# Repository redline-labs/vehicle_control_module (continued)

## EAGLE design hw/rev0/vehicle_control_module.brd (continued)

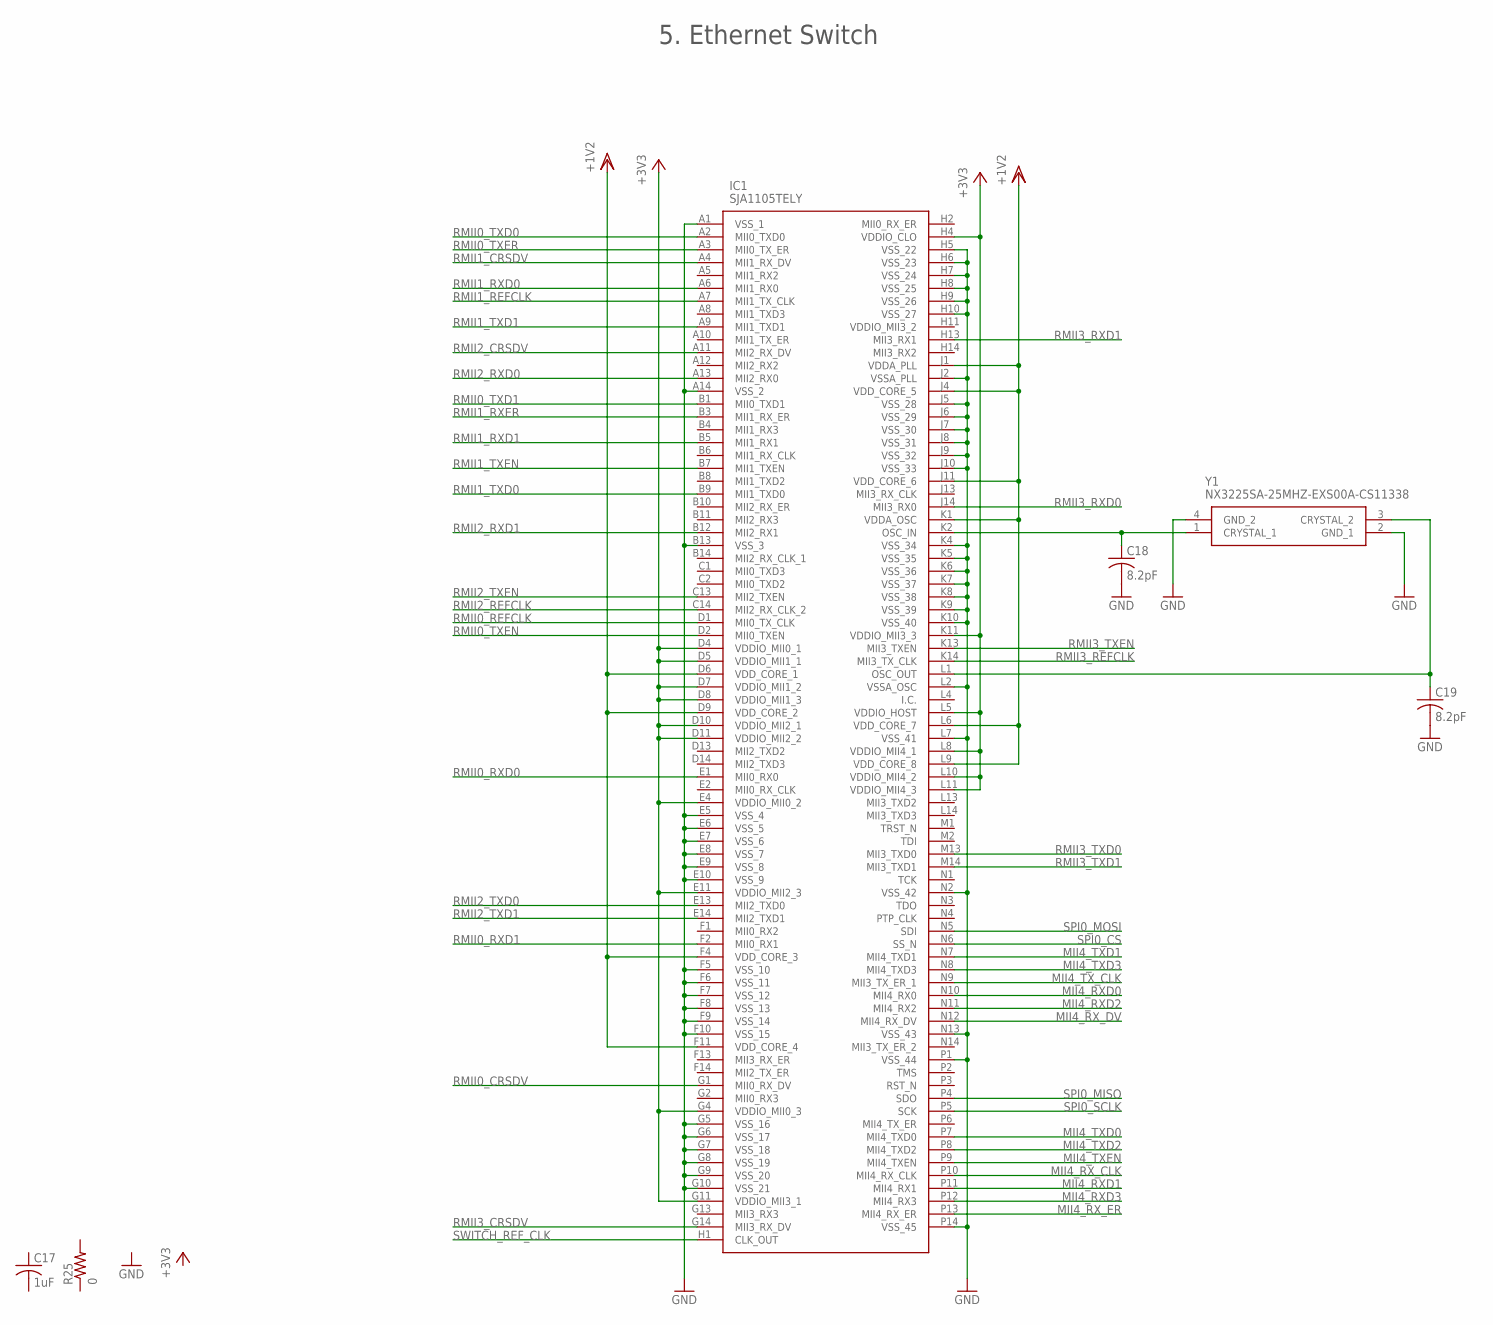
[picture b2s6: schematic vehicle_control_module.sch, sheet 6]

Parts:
C17: 1uF; C0603
C18, C19: 8.2pF; C0603
IC1: SJA1105TELY; BGA159C80P14X14_1200X1200X150
R25: 0; R0603
Y1: NX3225SA-25MHZ-EXS00A-CS11338; NX3225SA25MHZEXS00ACS11338

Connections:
+3V3: IC1.D4 (VDDIO_MII0_1), IC1.D5 (VDDIO_MII1_1), IC1.D7 (VDDIO_MII1_2), IC1.D8 (VDDIO_MII1_3), IC1.D10 (VDDIO_MII2_1), IC1.D11 (VDDIO_MII2_2), IC1.E4 (VDDIO_MII0_2), IC1.E11 (VDDIO_MII2_3), IC1.G4 (VDDIO_MII0_3), IC1.G11 (VDDIO_MII3_1), IC1.H4 (VDDIO_CLO), IC1.K11 (VDDIO_MII3_3), IC1.L5 (VDDIO_HOST), IC1.L8 (VDDIO_MII4_1), IC1.L10 (VDDIO_MII4_2), IC1.L11 (VDDIO_MII4_3); also elsewhere on the board
GND: C18.2, C19.2, IC1.A1 (VSS_1), IC1.A14 (VSS_2), IC1.B13 (VSS_3), IC1.E5 (VSS_4), IC1.E6 (VSS_5), IC1.E7 (VSS_6), IC1.E8 (VSS_7), IC1.E9 (VSS_8), IC1.E10 (VSS_9), IC1.F5 (VSS_10), IC1.F6 (VSS_11), IC1.F7 (VSS_12), IC1.F8 (VSS_13), IC1.F9 (VSS_14), IC1.F10 (VSS_15), IC1.G5 (VSS_16), IC1.G6 (VSS_17), IC1.G7 (VSS_18), IC1.G8 (VSS_19), IC1.G9 (VSS_20), IC1.G10 (VSS_21), IC1.H5 (VSS_22), IC1.H6 (VSS_23), IC1.H7 (VSS_24), IC1.H8 (VSS_25), IC1.H9 (VSS_26), IC1.H10 (VSS_27), IC1.J2 (VSSA_PLL), IC1.J5 (VSS_28), IC1.J6 (VSS_29), IC1.J7 (VSS_30), IC1.J8 (VSS_31), IC1.J9 (VSS_32), IC1.J10 (VSS_33), IC1.K4 (VSS_34), IC1.K5 (VSS_35), IC1.K6 (VSS_36), IC1.K7 (VSS_37), IC1.K8 (VSS_38), IC1.K9 (VSS_39), IC1.K10 (VSS_40), IC1.L2 (VSSA_OSC), IC1.L7 (VSS_41), IC1.N2 (VSS_42), IC1.N13 (VSS_43), IC1.P1 (VSS_44), IC1.P14 (VSS_45), Y1.2 (GND_1), Y1.4 (GND_2); also elsewhere on the board
MII4_RXD0: IC1.N10 (MII4_RX0); also elsewhere on the board
MII4_RXD1: IC1.P11 (MII4_RX1); also elsewhere on the board
MII4_RXD2: IC1.N11 (MII4_RX2); also elsewhere on the board
MII4_RXD3: IC1.P12 (MII4_RX3); also elsewhere on the board
MII4_RX_CLK: IC1.P10 (MII4_RX_CLK); also elsewhere on the board
MII4_RX_DV: IC1.N12 (MII4_RX_DV); also elsewhere on the board
MII4_RX_ER: IC1.P13 (MII4_RX_ER)
MII4_TXD0: IC1.P7 (MII4_TXD0); also elsewhere on the board
MII4_TXD1: IC1.N7 (MII4_TXD1); also elsewhere on the board
MII4_TXD2: IC1.P8 (MII4_TXD2); also elsewhere on the board
MII4_TXD3: IC1.N8 (MII4_TXD3); also elsewhere on the board
MII4_TXEN: IC1.P9 (MII4_TXEN); also elsewhere on the board
MII4_TX_CLK: IC1.N9 (MII3_TX_ER_1); also elsewhere on the board
unnamed: C18.1, IC1.K2 (OSC_IN), Y1.1 (CRYSTAL_1)
unnamed: C19.1, IC1.L1 (OSC_OUT), Y1.3 (CRYSTAL_2)
RMII0_CRSDV: IC1.G1 (MII0_RX_DV); also elsewhere on the board
RMII0_REFCLK: IC1.D1 (MII0_TX_CLK); also elsewhere on the board
RMII0_RXD0: IC1.E1 (MII0_RX0); also elsewhere on the board
RMII0_RXD1: IC1.F2 (MII0_RX1); also elsewhere on the board
RMII0_TXD0: IC1.A2 (MII0_TXD0); also elsewhere on the board
RMII0_TXD1: IC1.B1 (MII0_TXD1); also elsewhere on the board
RMII0_TXEN: IC1.D2 (MII0_TXEN); also elsewhere on the board
RMII0_TXER: IC1.A3 (MII0_TX_ER); also elsewhere on the board
RMII1_CRSDV: IC1.A4 (MII1_RX_DV); also elsewhere on the board
RMII1_REFCLK: IC1.A7 (MII1_TX_CLK); also elsewhere on the board
RMII1_RXD0: IC1.A6 (MII1_RX0); also elsewhere on the board
RMII1_RXD1: IC1.B5 (MII1_RX1); also elsewhere on the board
RMII1_RXER: IC1.B3 (MII1_RX_ER); also elsewhere on the board
RMII1_TXD0: IC1.B9 (MII1_TXD0); also elsewhere on the board
RMII1_TXD1: IC1.A9 (MII1_TXD1); also elsewhere on the board
RMII1_TXEN: IC1.B7 (MII1_TXEN)
RMII2_CRSDV: IC1.A11 (MII2_RX_DV); also elsewhere on the board
RMII2_REFCLK: IC1.C14 (MII2_RX_CLK_2); also elsewhere on the board
RMII2_RXD0: IC1.A13 (MII2_RX0); also elsewhere on the board
RMII2_RXD1: IC1.B12 (MII2_RX1); also elsewhere on the board
RMII2_TXD0: IC1.E13 (MII2_TXD0); also elsewhere on the board
RMII2_TXD1: IC1.E14 (MII2_TXD1); also elsewhere on the board
RMII2_TXEN: IC1.C13 (MII2_TXEN)
RMII3_CRSDV: IC1.G14 (MII3_RX_DV); also elsewhere on the board
RMII3_REFCLK: IC1.K14 (MII3_TX_CLK); also elsewhere on the board
RMII3_RXD0: IC1.J14 (MII3_RX0); also elsewhere on the board
RMII3_RXD1: IC1.H13 (MII3_RX1); also elsewhere on the board
RMII3_TXD0: IC1.M13 (MII3_TXD0); also elsewhere on the board
RMII3_TXD1: IC1.M14 (MII3_TXD1); also elsewhere on the board
RMII3_TXEN: IC1.K13 (MII3_TXEN)
SPI0_CS: IC1.N6 (SS_N); also elsewhere on the board
SPI0_MISO: IC1.P4 (SDO); also elsewhere on the board
SPI0_MOSI: IC1.N5 (SDI); also elsewhere on the board
SPI0_SCLK: IC1.P5 (SCK); also elsewhere on the board
SWITCH_REF_CLK: IC1.H1 (CLK_OUT); also elsewhere on the board
VDD: IC1.D6 (VDD_CORE_1), IC1.D9 (VDD_CORE_2), IC1.F4 (VDD_CORE_3), IC1.F11 (VDD_CORE_4), IC1.J1 (VDDA_PLL), IC1.J4 (VDD_CORE_5), IC1.J11 (VDD_CORE_6), IC1.K1 (VDDA_OSC), IC1.L6 (VDD_CORE_7), IC1.L9 (VDD_CORE_8); also elsewhere on the board

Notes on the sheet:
5. Ethernet Switch

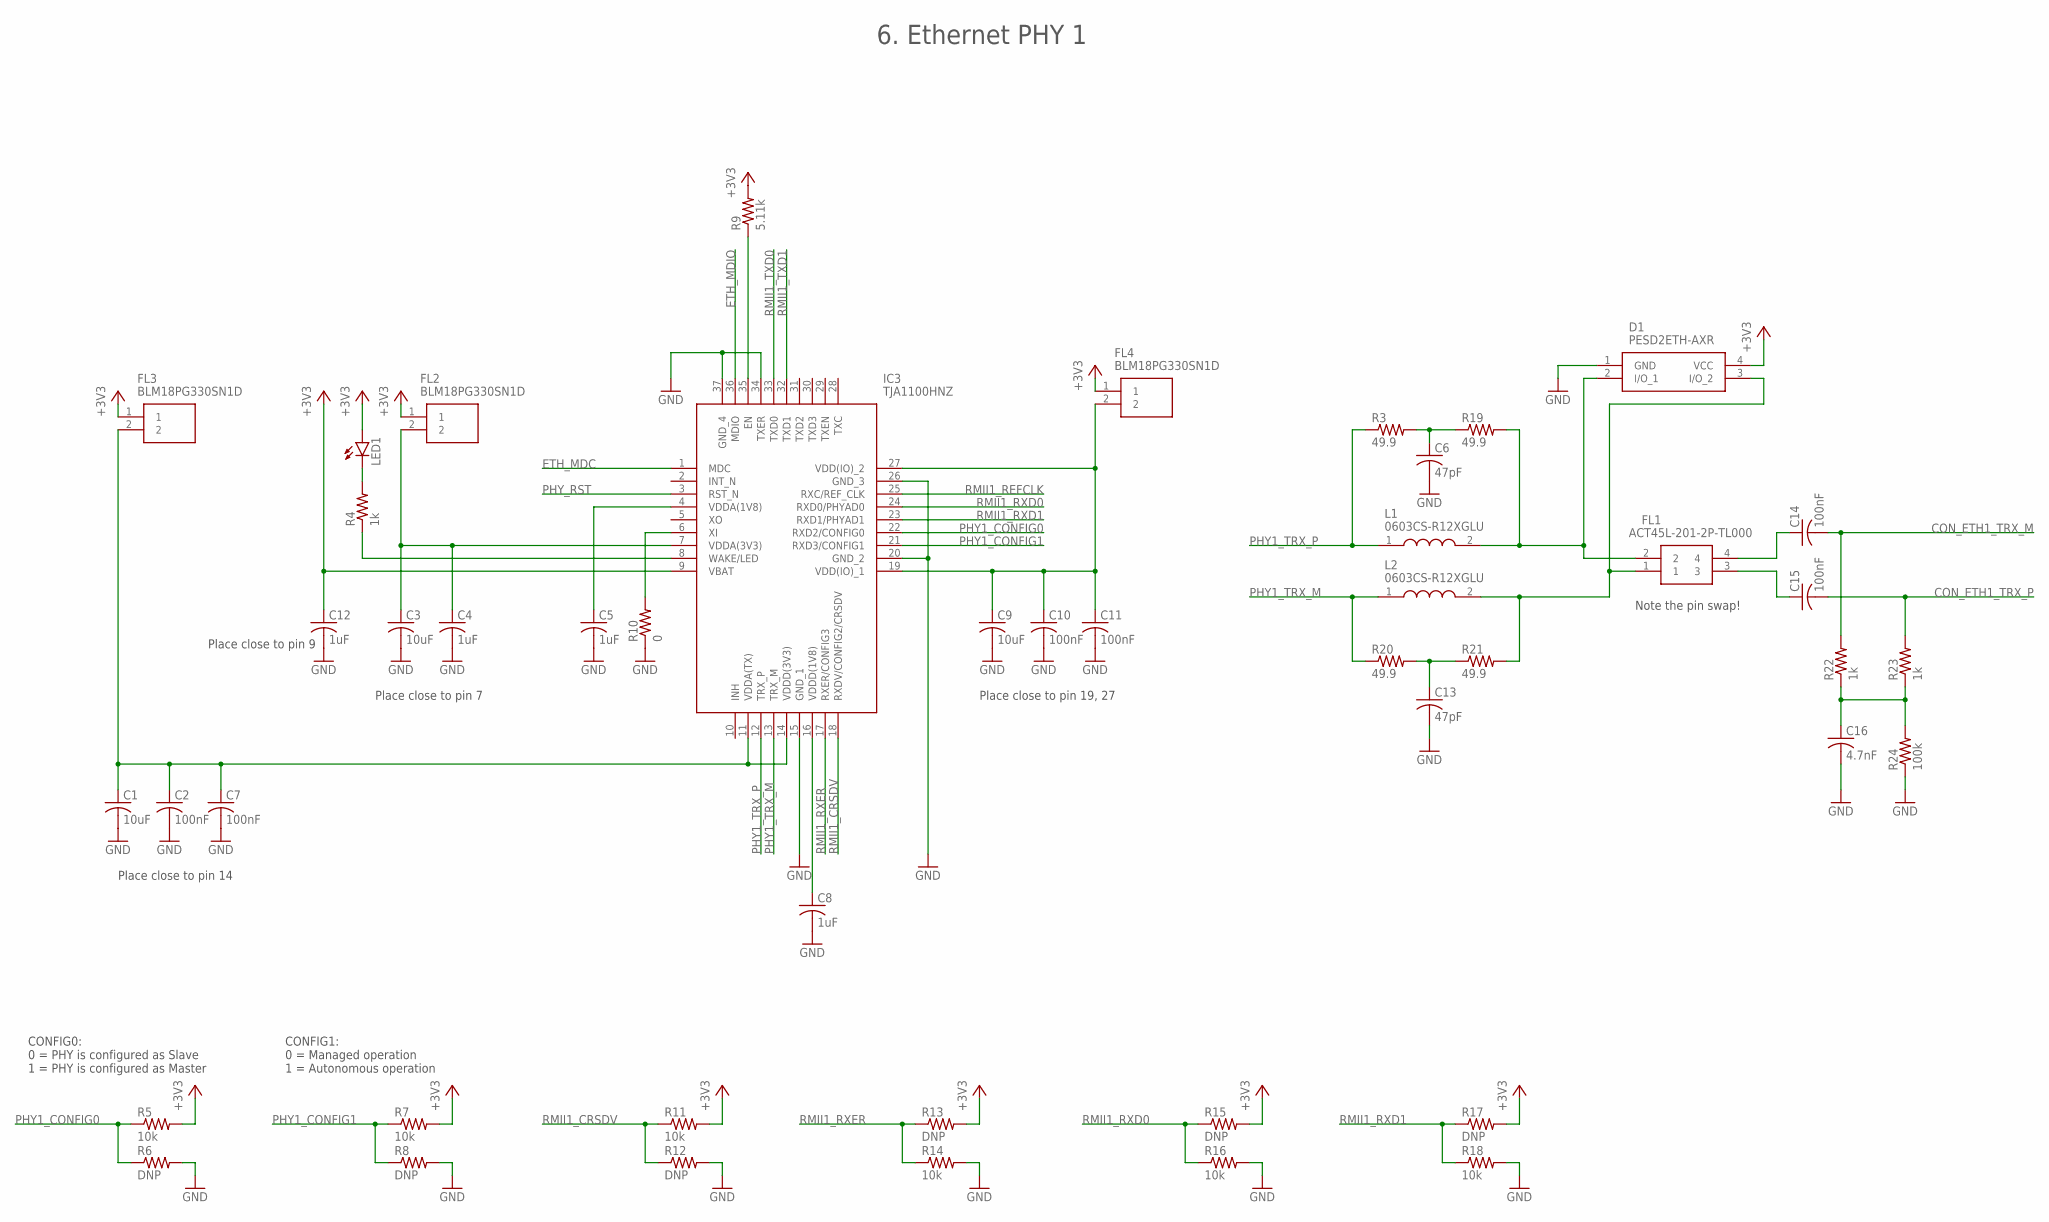
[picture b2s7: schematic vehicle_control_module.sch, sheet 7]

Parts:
C1, C3, C9: 10uF; C0603
C2, C7, C10, C11, C14, C15: 100nF; C0603
C4, C5, C8, C12: 1uF; C0603
C6, C13: 47pF; C0603
C16: 4.7nF; C0603
D1: PESD2ETH-AXR; PESD2ETHAXR
FL1: ACT45L-201-2P-TL000; ACT45L_1
FL2, FL3, FL4: BLM18PG330SN1D; BEADC1608X95N
IC3: TJA1100HNZ; QFN50P600X600X100-37N
L1, L2: 0603CS-R12XGLU; 0603CS82NXGLW
LED1: LEDCHIPLED_0603; CHIPLED_0603
R3, R19, R20, R21: 49.9; R0603
R4, R22, R23: 1k; R0603
R5, R7, R11, R14, R16, R18: 10k; R0603
R6, R8, R12, R13, R15, R17: DNP; R0603
R9: 5.11k; R0603
R10: 0; R0603
R24: 100k; R0603

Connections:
+3V3: C12.1, D1.4 (VCC), FL2.1, FL3.1, FL4.1, IC3.9 (VBAT), LED1.A, R5.2, R7.2, R9.2, R11.2, R13.2, R15.2, R17.2; also elsewhere on the board
CON_ETH1_TRX_M: C14.2, R22.2
CON_ETH1_TRX_P: C15.2, R23.2
ETH_MDC: IC3.1 (MDC); also elsewhere on the board
ETH_MDIO: IC3.36 (MDIO); also elsewhere on the board
GND: C1.2, C2.2, C3.2, C4.2, C5.2, C6.2, C7.2, C8.2, C9.2, C10.2, C11.2, C12.2, C13.2, C16.2, D1.1 (GND), IC3.15 (GND_1), IC3.20 (GND_2), IC3.26 (GND_3), IC3.34 (TXER), IC3.37 (GND_4), R6.2, R8.2, R10.1, R12.2, R14.2, R16.2, R18.2, R24.1; also elsewhere on the board
unnamed: LED1.C, R4.2
unnamed: C5.1, IC3.4 (VDDA(1V8))
unnamed: IC3.8 (WAKE/LED), R4.1
unnamed: C8.1, IC3.16 (VDDD(1V8))
unnamed: C3.1, C4.1, FL2.2, IC3.7 (VDDA(3V3))
unnamed: C1.1, C2.1, C7.1, FL3.2, IC3.11 (VDDA(TX)), IC3.14 (VDDD(3V3))
unnamed: C9.1, C10.1, C11.1, FL4.2, IC3.19 (VDD(IO)_1), IC3.27 (VDD(IO)_2)
unnamed: IC3.35 (EN), R9.1
unnamed: IC3.6 (XI), R10.2
unnamed: D1.3 (I/O_2), FL1.1, L2.2, R21.2
unnamed: D1.2 (I/O_1), FL1.2, L1.2, R19.2
unnamed: C6.1, R3.2, R19.1
unnamed: C13.1, R20.2, R21.1
unnamed: C14.1, FL1.4
unnamed: C15.1, FL1.3
unnamed: C16.1, R22.1, R23.1, R24.2
PHY1_CONFIG0: IC3.22 (RXD2/CONFIG0), R5.1, R6.1
PHY1_CONFIG1: IC3.21 (RXD3/CONFIG1), R7.1, R8.1
PHY1_TRX_M: IC3.13 (TRX_M), L2.1, R20.1
PHY1_TRX_P: IC3.12 (TRX_P), L1.1, R3.1
PHY_RST: IC3.3 (RST_N); also elsewhere on the board
RMII1_CRSDV: IC3.18 (RXDV/CONFIG2/CRSDV), R11.1, R12.1; also elsewhere on the board
RMII1_REFCLK: IC3.25 (RXC/REF_CLK); also elsewhere on the board
RMII1_RXD0: IC3.24 (RXD0/PHYAD0), R15.1, R16.1; also elsewhere on the board
RMII1_RXD1: IC3.23 (RXD1/PHYAD1), R17.1, R18.1; also elsewhere on the board
RMII1_RXER: IC3.17 (RXER/CONFIG3), R13.1, R14.1; also elsewhere on the board
RMII1_TXD0: IC3.33 (TXD0); also elsewhere on the board
RMII1_TXD1: IC3.32 (TXD1); also elsewhere on the board

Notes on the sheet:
Place close to pin 7
Place close to pin 9
Place close to pin 14
Place close to pin 19, 27
CONFIG0: 0 = PHY is configured as Slave 1 = PHY is configured as Master
CONFIG1: 0 = Managed operation 1 = Autonomous operation
Note the pin swap!
6. Ethernet PHY 1

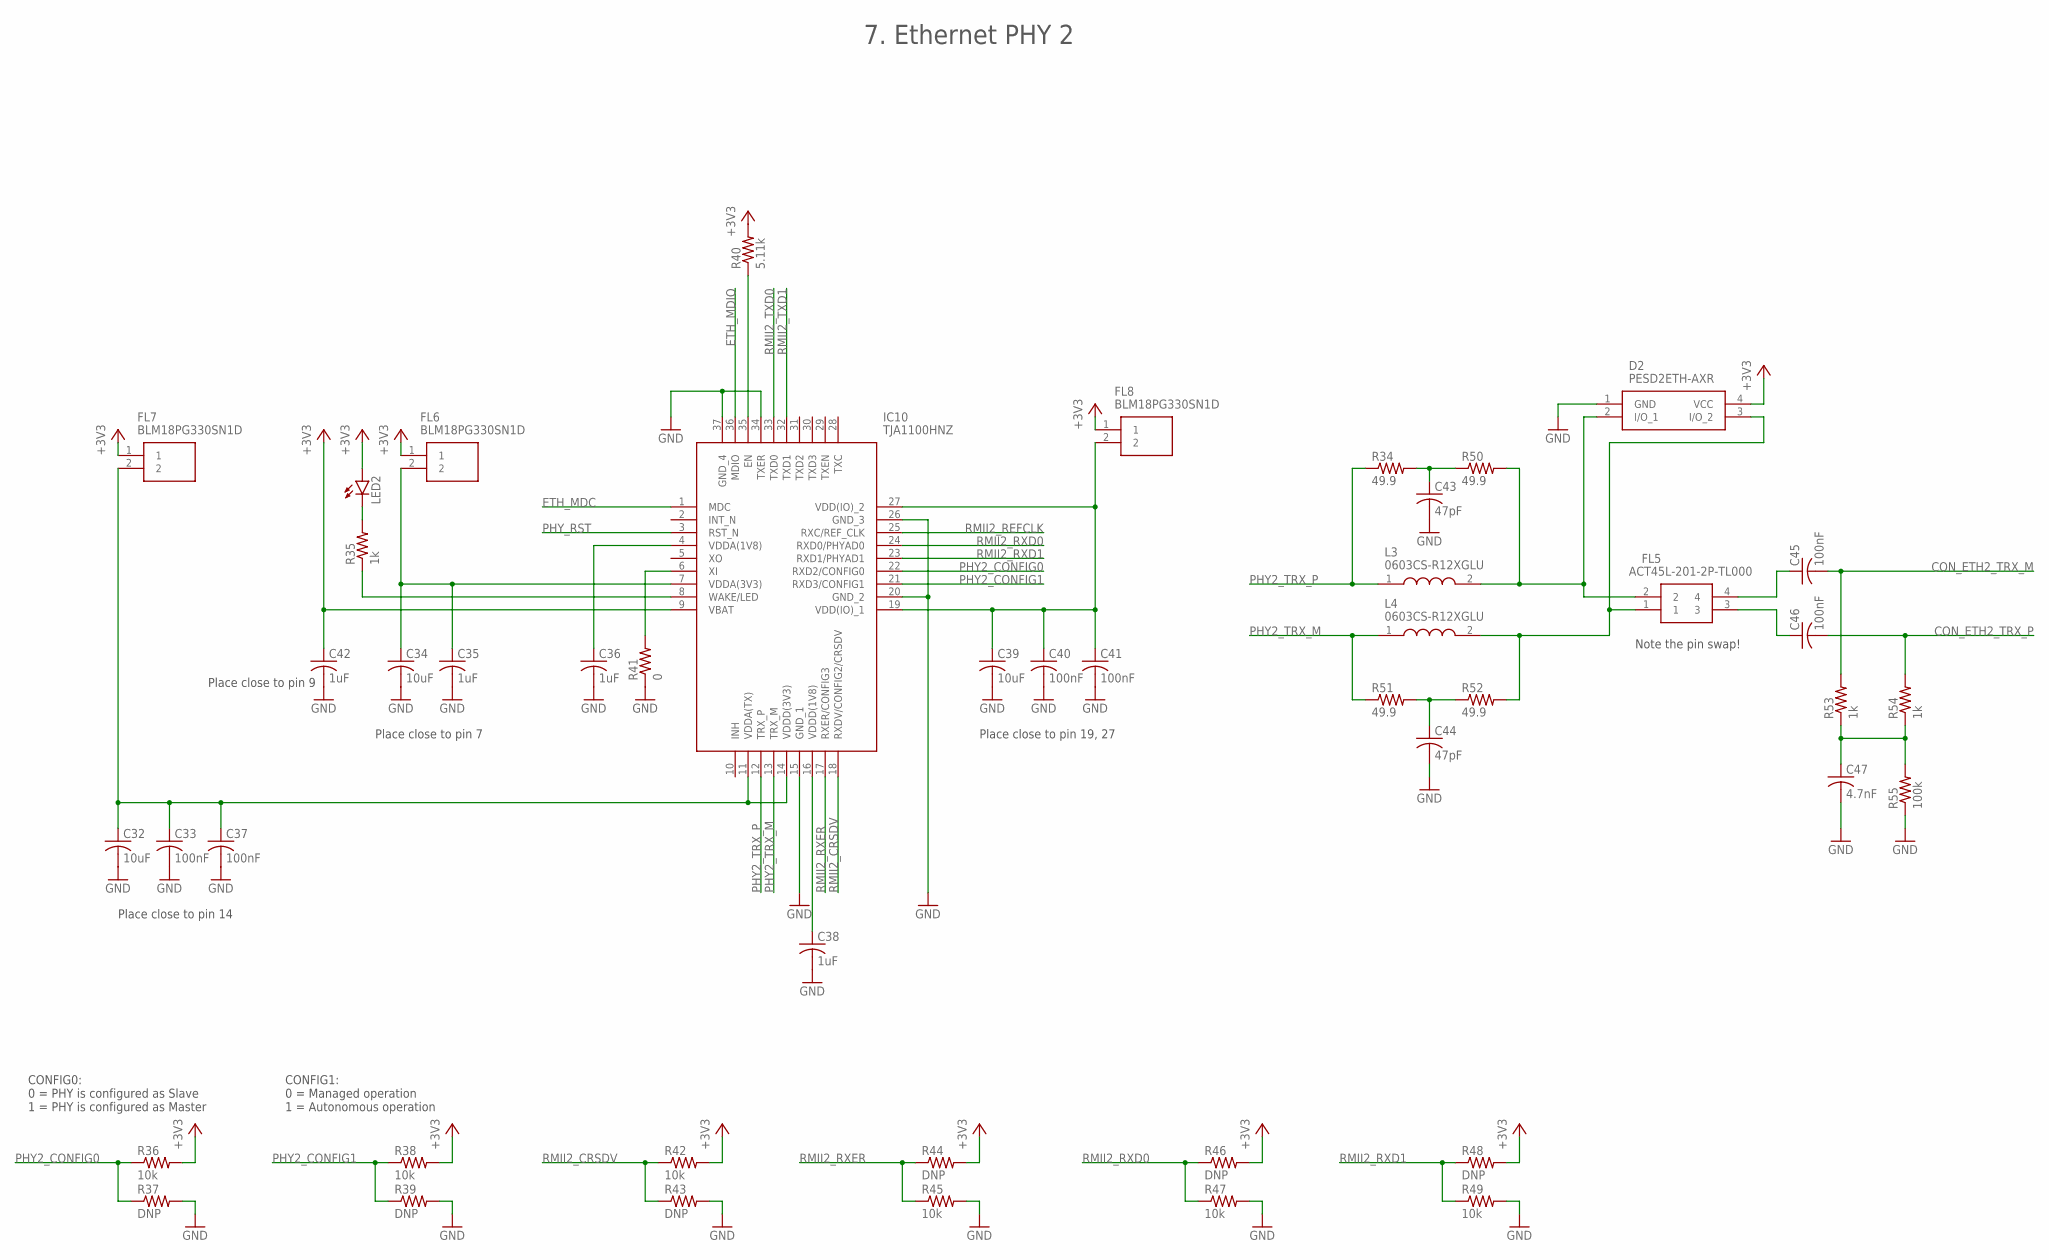
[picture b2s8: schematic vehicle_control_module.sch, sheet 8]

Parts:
C32, C34, C39: 10uF; C0603
C33, C37, C40, C41, C45, C46: 100nF; C0603
C35, C36, C38, C42: 1uF; C0603
C43, C44: 47pF; C0603
C47: 4.7nF; C0603
D2: PESD2ETH-AXR; PESD2ETHAXR
FL5: ACT45L-201-2P-TL000; ACT45L_1
FL6, FL7, FL8: BLM18PG330SN1D; BEADC1608X95N
IC10: TJA1100HNZ; QFN50P600X600X100-37N
L3, L4: 0603CS-R12XGLU; 0603CS82NXGLW
LED2: LEDCHIPLED_0603; CHIPLED_0603
R34, R50, R51, R52: 49.9; R0603
R35, R53, R54: 1k; R0603
R36, R38, R42, R45, R47, R49: 10k; R0603
R37, R39, R43, R44, R46, R48: DNP; R0603
R40: 5.11k; R0603
R41: 0; R0603
R55: 100k; R0603

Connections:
+3V3: C42.1, D2.4 (VCC), FL6.1, FL7.1, FL8.1, IC10.9 (VBAT), LED2.A, R36.2, R38.2, R40.2, R42.2, R44.2, R46.2, R48.2; also elsewhere on the board
CON_ETH2_TRX_M: C45.2, R53.2
CON_ETH2_TRX_P: C46.2, R54.2
ETH_MDC: IC10.1 (MDC); also elsewhere on the board
ETH_MDIO: IC10.36 (MDIO); also elsewhere on the board
GND: C32.2, C33.2, C34.2, C35.2, C36.2, C37.2, C38.2, C39.2, C40.2, C41.2, C42.2, C43.2, C44.2, C47.2, D2.1 (GND), IC10.15 (GND_1), IC10.20 (GND_2), IC10.26 (GND_3), IC10.34 (TXER), IC10.37 (GND_4), R37.2, R39.2, R41.1, R43.2, R45.2, R47.2, R49.2, R55.1; also elsewhere on the board
unnamed: LED2.C, R35.2
unnamed: IC10.8 (WAKE/LED), R35.1
unnamed: C36.1, IC10.4 (VDDA(1V8))
unnamed: C38.1, IC10.16 (VDDD(1V8))
unnamed: C34.1, C35.1, FL6.2, IC10.7 (VDDA(3V3))
unnamed: C32.1, C33.1, C37.1, FL7.2, IC10.11 (VDDA(TX)), IC10.14 (VDDD(3V3))
unnamed: C39.1, C40.1, C41.1, FL8.2, IC10.19 (VDD(IO)_1), IC10.27 (VDD(IO)_2)
unnamed: IC10.35 (EN), R40.1
unnamed: IC10.6 (XI), R41.2
unnamed: D2.3 (I/O_2), FL5.1, L4.2, R52.2
unnamed: D2.2 (I/O_1), FL5.2, L3.2, R50.2
unnamed: C43.1, R34.2, R50.1
unnamed: C44.1, R51.2, R52.1
unnamed: C45.1, FL5.4
unnamed: C46.1, FL5.3
unnamed: C47.1, R53.1, R54.1, R55.2
PHY2_CONFIG0: IC10.22 (RXD2/CONFIG0), R36.1, R37.1
PHY2_CONFIG1: IC10.21 (RXD3/CONFIG1), R38.1, R39.1
PHY2_TRX_M: IC10.13 (TRX_M), L4.1, R51.1
PHY2_TRX_P: IC10.12 (TRX_P), L3.1, R34.1
PHY_RST: IC10.3 (RST_N); also elsewhere on the board
RMII2_CRSDV: IC10.18 (RXDV/CONFIG2/CRSDV), R42.1, R43.1; also elsewhere on the board
RMII2_REFCLK: IC10.25 (RXC/REF_CLK); also elsewhere on the board
RMII2_RXD0: IC10.24 (RXD0/PHYAD0), R46.1, R47.1; also elsewhere on the board
RMII2_RXD1: IC10.23 (RXD1/PHYAD1), R48.1, R49.1; also elsewhere on the board
RMII2_RXER: IC10.17 (RXER/CONFIG3), R44.1, R45.1
RMII2_TXD0: IC10.33 (TXD0); also elsewhere on the board
RMII2_TXD1: IC10.32 (TXD1); also elsewhere on the board

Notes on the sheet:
Place close to pin 7
Place close to pin 9
Place close to pin 14
Place close to pin 19, 27
CONFIG0: 0 = PHY is configured as Slave 1 = PHY is configured as Master
CONFIG1: 0 = Managed operation 1 = Autonomous operation
Note the pin swap!
7. Ethernet PHY 2

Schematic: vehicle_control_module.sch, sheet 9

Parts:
C48, C50, C55: 10uF; C0603
C49, C53, C56, C57, C61, C62: 100nF; C0603
C51, C52, C54, C58: 1uF; C0603
C59, C60: 47pF; C0603
C63: 4.7nF; C0603
D3: PESD2ETH-AXR; PESD2ETHAXR
FL9: ACT45L-201-2P-TL000; ACT45L_1
FL10, FL11, FL12: BLM18PG330SN1D; BEADC1608X95N
IC12: TJA1100HNZ; QFN50P600X600X100-37N
L5, L6: 0603CS-R12XGLU; 0603CS82NXGLW
LED3: LEDCHIPLED_0603; CHIPLED_0603
R56, R72, R73, R74: 49.9; R0603
R57, R75, R76: 1k; R0603
R58, R60, R64, R67, R69, R71: 10k; R0603
R59, R61, R65, R66, R68, R70: DNP; R0603
R62: 5.11k; R0603
R63: 0; R0603
R77: 100k; R0603

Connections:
+3V3: C58.1, D3.4 (VCC), FL10.1, FL11.1, FL12.1, IC12.9 (VBAT), LED3.A, R58.2, R60.2, R62.2, R64.2, R66.2, R68.2, R70.2; also elsewhere on the board
CON_ETH3_TRX_M: C61.2, R75.2
CON_ETH3_TRX_P: C62.2, R76.2
ETH_MDC: IC12.1 (MDC); also elsewhere on the board
ETH_MDIO: IC12.36 (MDIO); also elsewhere on the board
GND: C48.2, C49.2, C50.2, C51.2, C52.2, C53.2, C54.2, C55.2, C56.2, C57.2, C58.2, C59.2, C60.2, C63.2, D3.1 (GND), IC12.15 (GND_1), IC12.20 (GND_2), IC12.26 (GND_3), IC12.34 (TXER), IC12.37 (GND_4), R59.2, R61.2, R63.1, R65.2, R67.2, R69.2, R71.2, R77.1; also elsewhere on the board
unnamed: LED3.C, R57.2
unnamed: IC12.8 (WAKE/LED), R57.1
unnamed: C52.1, IC12.4 (VDDA(1V8))
unnamed: C54.1, IC12.16 (VDDD(1V8))
unnamed: C50.1, C51.1, FL10.2, IC12.7 (VDDA(3V3))
unnamed: C48.1, C49.1, C53.1, FL11.2, IC12.11 (VDDA(TX)), IC12.14 (VDDD(3V3))
unnamed: C55.1, C56.1, C57.1, FL12.2, IC12.19 (VDD(IO)_1), IC12.27 (VDD(IO)_2)
unnamed: IC12.35 (EN), R62.1
unnamed: IC12.6 (XI), R63.2
unnamed: D3.3 (I/O_2), FL9.1, L6.2, R74.2
unnamed: D3.2 (I/O_1), FL9.2, L5.2, R72.2
unnamed: C59.1, R56.2, R72.1
unnamed: C60.1, R73.2, R74.1
unnamed: C61.1, FL9.4
unnamed: C62.1, FL9.3
unnamed: C63.1, R75.1, R76.1, R77.2
PHY3_CONFIG0: IC12.22 (RXD2/CONFIG0), R58.1, R59.1
PHY3_CONFIG1: IC12.21 (RXD3/CONFIG1), R60.1, R61.1
PHY3_TRX_M: IC12.13 (TRX_M), L6.1, R73.1
PHY3_TRX_P: IC12.12 (TRX_P), L5.1, R56.1
PHY_RST: IC12.3 (RST_N); also elsewhere on the board
RMII3_CRSDV: IC12.18 (RXDV/CONFIG2/CRSDV), R64.1, R65.1; also elsewhere on the board
RMII3_REFCLK: IC12.25 (RXC/REF_CLK); also elsewhere on the board
RMII3_RXD0: IC12.24 (RXD0/PHYAD0), R68.1, R69.1; also elsewhere on the board
RMII3_RXD1: IC12.23 (RXD1/PHYAD1), R70.1, R71.1; also elsewhere on the board
RMII3_RXER: IC12.17 (RXER/CONFIG3), R66.1, R67.1
RMII3_TXD0: IC12.33 (TXD0); also elsewhere on the board
RMII3_TXD1: IC12.32 (TXD1); also elsewhere on the board

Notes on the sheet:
Place close to pin 7
Place close to pin 9
Place close to pin 14
Place close to pin 19, 27
CONFIG0: 0 = PHY is configured as Slave 1 = PHY is configured as Master
CONFIG1: 0 = Managed operation 1 = Autonomous operation
Note the pin swap!
8. Ethernet PHY 3

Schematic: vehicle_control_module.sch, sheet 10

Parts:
C23, C25, C28: 10uF; C0603
C24, C26, C27, C29: 0.1uF; C0603
IC11: KSZ8061MNXI-TR; QFN50P500X500X85-33N
R31: 6.04k; R0603
R32: 4.7k; R0603

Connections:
+3V3: C23.1, C24.1, IC11.3 (AVDDH), IC11.15 (VDDIO), R32.1; also elsewhere on the board
DEBUG_ETH_CONFIG1: IC11.27 (CRS), R32.2
DEBUG_ETH_LED0: IC11.24 (LED0/TXER); also elsewhere on the board
DEBUG_ETH_LED1: IC11.32 (SIGDET); also elsewhere on the board
DEBUG_ETH_RXM: IC11.7 (RXM); also elsewhere on the board
DEBUG_ETH_RXP: IC11.6 (RXP); also elsewhere on the board
DEBUG_ETH_TXM: IC11.5 (TXM); also elsewhere on the board
DEBUG_ETH_TXP: IC11.4 (TXP); also elsewhere on the board
ETH_MDC: IC11.11 (MDC); also elsewhere on the board
ETH_MDIO: IC11.10 (MDIO); also elsewhere on the board
GND: C23.2, C24.2, C25.2, C26.2, C27.2, C28.2, C29.2, IC11.33 (PADDLE), R31.1; also elsewhere on the board
MII4_RXD0: IC11.18 (RXD0); also elsewhere on the board
MII4_RXD1: IC11.17 (RXD1); also elsewhere on the board
MII4_RXD2: IC11.16 (RXD2); also elsewhere on the board
MII4_RXD3: IC11.14 (RXD3); also elsewhere on the board
MII4_RXERR: IC11.12 (RXERR)
MII4_RX_CLK: IC11.19 (RXC); also elsewhere on the board
MII4_RX_DV: IC11.13 (RXDV); also elsewhere on the board
MII4_TXD0: IC11.22 (TXD0); also elsewhere on the board
MII4_TXD1: IC11.23 (TXD1); also elsewhere on the board
MII4_TXD2: IC11.25 (TXD2); also elsewhere on the board
MII4_TXD3: IC11.26 (TXD3); also elsewhere on the board
MII4_TXEN: IC11.21 (TXEN); also elsewhere on the board
MII4_TX_CLK: IC11.20 (TXC); also elsewhere on the board
unnamed: IC11.31 (REXT), R31.2
PHY_RESET: IC11.28 (!RESET)
SWITCH_REF_CLK: IC11.1 (XI); also elsewhere on the board
VDD: C25.1, C26.1, C27.1, C28.1, C29.1, IC11.8 (AVDDL), IC11.9 (VDDL_1), IC11.30 (VDDL_2); also elsewhere on the board

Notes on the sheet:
9. Ethernet PHY 4

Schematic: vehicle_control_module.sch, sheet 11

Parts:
C128, C130, C132, C134, C136, C138, C140, C142, C144: 0.01uF; C0603
C129, C131, C133, C135, C137, C139, C141, C143, C145: 150nF; C0603
D19, D20, D21, D22, D23, D24, D25, D26, D27: BAT54SWFILMY; SOT65P210X110-3N
R150, R155, R160, R165, R170, R175, R180, R185, R190: 4; R1206
R151, R154, R156, R159, R161, R164, R166, R169, R171, R174, R176, R179, R181, R184, R186, R189, R191, R194: 4.7k; R0603
R152, R157, R162, R167, R172, R177, R182, R187, R192: 2.74k; R0603
U?10, U?11, U?12, U?13, U?14, U?15, U?16, U?17, U?18: BTS50015-1TAD; TO127P1500X450-7_8N-V1

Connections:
+3V3: D19.2 (K), D20.2 (K), D21.2 (K), D22.2 (K), D23.2 (K), D24.2 (K), D25.2 (K), D26.2 (K), D27.2 (K); also elsewhere on the board
ADC0_3: C128.1, D19.3 (A,K), R151.2; also elsewhere on the board
ADC0_4: C130.1, D20.3 (A,K), R156.2; also elsewhere on the board
ADC0_6: C132.1, D21.3 (A,K), R161.2; also elsewhere on the board
ADC0_7: C134.1, D22.3 (A,K), R166.2; also elsewhere on the board
ADC0_8: C136.1, D23.3 (A,K), R171.2; also elsewhere on the board
ADC0_9: C138.1, D24.3 (A,K), R176.2; also elsewhere on the board
ADC0_10: C140.1, D25.3 (A,K), R181.2; also elsewhere on the board
ADC1_0: C142.1, D26.3 (A,K), R186.2; also elsewhere on the board
ADC1_1: C144.1, D27.3 (A,K), R191.2; also elsewhere on the board
GND: C128.2, C130.2, C132.2, C134.2, C136.2, C138.2, C140.2, C142.2, C144.2, D19.1 (A), D20.1 (A), D21.1 (A), D22.1 (A), D23.1 (A), D24.1 (A), D25.1 (A), D26.1 (A), D27.1 (A), R150.2, R152.2, R155.2, R157.2, R160.2, R162.2, R165.2, R167.2, R170.2, R172.2, R175.2, R177.2, R180.2, R182.2, R185.2, R187.2, R190.2, R192.2; also elsewhere on the board
HIGHSIDE_0_EN: R154.2; also elsewhere on the board
HIGHSIDE_0_OUTPUT: U?10.5 (OUT1), U?10.6 (OUT2), U?10.7 (OUT3)
HIGHSIDE_1_EN: R159.2; also elsewhere on the board
HIGHSIDE_1_OUTPUT: U?11.5 (OUT1), U?11.6 (OUT2), U?11.7 (OUT3)
HIGHSIDE_2_EN: R164.2; also elsewhere on the board
HIGHSIDE_2_OUTPUT: U?12.5 (OUT1), U?12.6 (OUT2), U?12.7 (OUT3)
HIGHSIDE_3_EN: R169.2; also elsewhere on the board
HIGHSIDE_3_OUTPUT: U?13.5 (OUT1), U?13.6 (OUT2), U?13.7 (OUT3)
HIGHSIDE_4_EN: R174.2; also elsewhere on the board
HIGHSIDE_4_OUTPUT: U?14.5 (OUT1), U?14.6 (OUT2), U?14.7 (OUT3)
HIGHSIDE_5_EN: R179.2; also elsewhere on the board
HIGHSIDE_5_OUTPUT: U?15.5 (OUT1), U?15.6 (OUT2), U?15.7 (OUT3)
HIGHSIDE_6_EN: R184.2; also elsewhere on the board
HIGHSIDE_6_OUTPUT: U?16.5 (OUT1), U?16.6 (OUT2), U?16.7 (OUT3)
HIGHSIDE_7_EN: R189.2; also elsewhere on the board
HIGHSIDE_7_OUTPUT: U?17.5 (OUT1), U?17.6 (OUT2), U?17.7 (OUT3)
HIGHSIDE_8_EN: R194.2; also elsewhere on the board
HIGHSIDE_8_OUTPUT: U?18.5 (OUT1), U?18.6 (OUT2), U?18.7 (OUT3)
unnamed: C129.2, R150.1, U?10.1 (GND)
unnamed: R151.1, R152.1, U?10.3 (IS)
unnamed: C129.1, R154.1, U?10.2 (IN)
unnamed: C131.2, R155.1, U?11.1 (GND)
unnamed: R156.1, R157.1, U?11.3 (IS)
unnamed: C131.1, R159.1, U?11.2 (IN)
unnamed: C133.2, R160.1, U?12.1 (GND)
unnamed: R161.1, R162.1, U?12.3 (IS)
unnamed: C133.1, R164.1, U?12.2 (IN)
unnamed: C135.2, R165.1, U?13.1 (GND)
unnamed: R166.1, R167.1, U?13.3 (IS)
unnamed: C135.1, R169.1, U?13.2 (IN)
unnamed: C137.2, R170.1, U?14.1 (GND)
unnamed: R171.1, R172.1, U?14.3 (IS)
unnamed: C137.1, R174.1, U?14.2 (IN)
unnamed: C139.2, R175.1, U?15.1 (GND)
unnamed: R176.1, R177.1, U?15.3 (IS)
unnamed: C139.1, R179.1, U?15.2 (IN)
unnamed: C141.2, R180.1, U?16.1 (GND)
unnamed: R181.1, R182.1, U?16.3 (IS)
unnamed: C141.1, R184.1, U?16.2 (IN)
unnamed: C143.2, R185.1, U?17.1 (GND)
unnamed: R186.1, R187.1, U?17.3 (IS)
unnamed: C143.1, R189.1, U?17.2 (IN)
unnamed: C145.2, R190.1, U?18.1 (GND)
unnamed: R191.1, R192.1, U?18.3 (IS)
unnamed: C145.1, R194.1, U?18.2 (IN)
VBATT: U?10.8 (VS), U?11.8 (VS), U?12.8 (VS), U?13.8 (VS), U?14.8 (VS), U?15.8 (VS), U?16.8 (VS), U?17.8 (VS), U?18.8 (VS); also elsewhere on the board

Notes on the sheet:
10. High Side Drivers (1/2)
RC lowpass on IS results in ~3400Hz cutoff

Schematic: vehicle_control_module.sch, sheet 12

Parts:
C108, C111, C114, C116, C118, C120, C122, C124, C126: 0.01uF; C0603
C112, C113, C115, C117, C119, C121, C123, C125, C127: 150nF; C0603
D10, D11, D12, D13, D14, D15, D16, D17, D18: BAT54SWFILMY; SOT65P210X110-3N
R105, R106, R115, R120, R125, R130, R135, R140, R145: 4; R1206
R107, R110, R111, R114, R116, R119, R121, R124, R126, R129, R131, R134, R136, R139, R141, R144, R146, R149: 4.7k; R0603
R108, R112, R117, R122, R127, R132, R137, R142, R147: 2.74k; R0603
U?1, U?2, U?3, U?4, U?5, U?6, U?7, U?8, U?9: BTS50015-1TAD; TO127P1500X450-7_8N-V1

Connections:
+3V3: D10.2 (K), D11.2 (K), D12.2 (K), D13.2 (K), D14.2 (K), D15.2 (K), D16.2 (K), D17.2 (K), D18.2 (K); also elsewhere on the board
ADC1_2: C111.1, D10.3 (A,K), R107.2; also elsewhere on the board
ADC1_4: C108.1, D11.3 (A,K), R111.2; also elsewhere on the board
ADC1_5: C114.1, D12.3 (A,K), R116.2; also elsewhere on the board
ADC1_6: C116.1, D13.3 (A,K), R121.2; also elsewhere on the board
ADC1_7: C118.1, D14.3 (A,K), R126.2; also elsewhere on the board
ADC1_8: C120.1, D15.3 (A,K), R131.2; also elsewhere on the board
ADC1_9: C122.1, D16.3 (A,K), R136.2; also elsewhere on the board
ADC1_10: C124.1, D17.3 (A,K), R141.2; also elsewhere on the board
ADC1_11: C126.1, D18.3 (A,K), R146.2; also elsewhere on the board
GND: C108.2, C111.2, C114.2, C116.2, C118.2, C120.2, C122.2, C124.2, C126.2, D10.1 (A), D11.1 (A), D12.1 (A), D13.1 (A), D14.1 (A), D15.1 (A), D16.1 (A), D17.1 (A), D18.1 (A), R105.2, R106.2, R108.2, R112.2, R115.2, R117.2, R120.2, R122.2, R125.2, R127.2, R130.2, R132.2, R135.2, R137.2, R140.2, R142.2, R145.2, R147.2; also elsewhere on the board
HIGHSIDE_9_EN: R110.2; also elsewhere on the board
HIGHSIDE_9_OUTPUT: U?1.5 (OUT1), U?1.6 (OUT2), U?1.7 (OUT3)
HIGHSIDE_10_EN: R114.2; also elsewhere on the board
HIGHSIDE_10_OUTPUT: U?2.5 (OUT1), U?2.6 (OUT2), U?2.7 (OUT3)
HIGHSIDE_11_EN: R119.2; also elsewhere on the board
HIGHSIDE_11_OUTPUT: U?3.5 (OUT1), U?3.6 (OUT2), U?3.7 (OUT3)
HIGHSIDE_12_EN: R124.2; also elsewhere on the board
HIGHSIDE_12_OUTPUT: U?4.5 (OUT1), U?4.6 (OUT2), U?4.7 (OUT3)
HIGHSIDE_13_EN: R129.2; also elsewhere on the board
HIGHSIDE_13_OUTPUT: U?5.5 (OUT1), U?5.6 (OUT2), U?5.7 (OUT3)
HIGHSIDE_14_EN: R134.2; also elsewhere on the board
HIGHSIDE_14_OUTPUT: U?6.5 (OUT1), U?6.6 (OUT2), U?6.7 (OUT3)
HIGHSIDE_15_EN: R139.2; also elsewhere on the board
HIGHSIDE_15_OUTPUT: U?7.5 (OUT1), U?7.6 (OUT2), U?7.7 (OUT3)
HIGHSIDE_16_EN: R144.2; also elsewhere on the board
HIGHSIDE_16_OUTPUT: U?8.5 (OUT1), U?8.6 (OUT2), U?8.7 (OUT3)
HIGHSIDE_17_EN: R149.2; also elsewhere on the board
HIGHSIDE_17_OUTPUT: U?9.5 (OUT1), U?9.6 (OUT2), U?9.7 (OUT3)
unnamed: C112.2, R106.1, U?1.1 (GND)
unnamed: R107.1, R108.1, U?1.3 (IS)
unnamed: C113.2, R105.1, U?2.1 (GND)
unnamed: C112.1, R110.1, U?1.2 (IN)
unnamed: R111.1, R112.1, U?2.3 (IS)
unnamed: C113.1, R114.1, U?2.2 (IN)
unnamed: C115.2, R115.1, U?3.1 (GND)
unnamed: R116.1, R117.1, U?3.3 (IS)
unnamed: C115.1, R119.1, U?3.2 (IN)
unnamed: C117.2, R120.1, U?4.1 (GND)
unnamed: R121.1, R122.1, U?4.3 (IS)
unnamed: C117.1, R124.1, U?4.2 (IN)
unnamed: C119.2, R125.1, U?5.1 (GND)
unnamed: R126.1, R127.1, U?5.3 (IS)
unnamed: C119.1, R129.1, U?5.2 (IN)
unnamed: C121.2, R130.1, U?6.1 (GND)
unnamed: R131.1, R132.1, U?6.3 (IS)
unnamed: C121.1, R134.1, U?6.2 (IN)
unnamed: C123.2, R135.1, U?7.1 (GND)
unnamed: R136.1, R137.1, U?7.3 (IS)
unnamed: C123.1, R139.1, U?7.2 (IN)
unnamed: C125.2, R140.1, U?8.1 (GND)
unnamed: R141.1, R142.1, U?8.3 (IS)
unnamed: C125.1, R144.1, U?8.2 (IN)
unnamed: C127.2, R145.1, U?9.1 (GND)
unnamed: R146.1, R147.1, U?9.3 (IS)
unnamed: C127.1, R149.1, U?9.2 (IN)
VBATT: U?1.8 (VS), U?2.8 (VS), U?3.8 (VS), U?4.8 (VS), U?5.8 (VS), U?6.8 (VS), U?7.8 (VS), U?8.8 (VS), U?9.8 (VS); also elsewhere on the board

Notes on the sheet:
11. High Side Drivers (2/2)
RC lowpass on IS results in ~3400Hz cutoff

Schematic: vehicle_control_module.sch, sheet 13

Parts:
C90, C93: 4.7nF; C0603
C91, C94, C146, C147: 100nF; C0603
C92, C95: 10uF; C0603
IC13, IC18: TLE9250XSJXUMA1; SOIC127P602X173-8N
R1, R2, R95, R96: 60; R0805
R195, R196: 10k; R0603

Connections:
+3V3: C146.1, C147.1, IC13.5 (VIO), IC18.5 (VIO), R195.1, R196.1; also elsewhere on the board
+5V: C91.1, C92.1, C94.1, C95.1, IC13.3 (VCC), IC18.3 (VCC); also elsewhere on the board
CAN0_H: IC13.7 (CANH), R1.1
CAN0_L: IC13.6 (CANL), R2.2
CAN0_RW_MODE: IC13.8 (RM), R196.2; also elsewhere on the board
CAN0_RX: IC13.4 (RXD); also elsewhere on the board
CAN0_TX: IC13.1 (TXD); also elsewhere on the board
CAN1_H: IC18.7 (CANH), R95.1
CAN1_L: IC18.6 (CANL), R96.2
CAN1_RW_MODE: IC18.8 (RM), R195.2; also elsewhere on the board
CAN1_RX: IC18.4 (RXD); also elsewhere on the board
CAN1_TX: IC18.1 (TXD); also elsewhere on the board
GND: C90.2, C91.2, C92.2, C93.2, C94.2, C95.2, C146.2, C147.2, IC13.2 (GND), IC18.2 (GND); also elsewhere on the board
unnamed: C93.1, R95.2, R96.1
unnamed: C90.1, R1.2, R2.1

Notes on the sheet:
12. CAN

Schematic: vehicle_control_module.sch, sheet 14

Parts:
C96: 1uF; C0603
C97: UCZ1K151MNQ1MS; CAPAE1360X1450N
C98: 100nF; C0603
J15: 693022010811
J27: 2041119-2; 20411192
LED9: LEDCHIPLED_0603; CHIPLED_0603
R102: 10k; R0603

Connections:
+3V3: C96.1, C97.1 (+), C98.1, J27.2 (3.3VAUX), J27.24 (+3.3VAUX_1), J27.39 (+3.3VAUX_2), J27.41 (+3.3VAUX_3), J27.52 (+3.3VAUX_4), R102.1; also elsewhere on the board
GND: C96.2, C97.2 (-), C98.2, J15.5 (GND), J27.4 (GND_1), J27.9 (GND_2), J27.15 (GND_3), J27.18 (GND_4), J27.21 (GND_5), J27.26 (GND_6), J27.27 (GND_7), J27.29 (GND_8), J27.34 (GND_9), J27.35 (GND_10), J27.37 (GND_11), J27.40 (GND_12), J27.43 (GND_13), J27.45 (RESERVED_1), J27.50 (GND_14); also elsewhere on the board
HOST_USB_DM: J27.36 (USB_D-); also elsewhere on the board
HOST_USB_DP: J27.38 (USB_D+); also elsewhere on the board
MODEM_DISABLE: J27.20 (W_DISABLE#); also elsewhere on the board
MODEM_RESET: J27.22 (PERST#); also elsewhere on the board
MODEM_WAN_LED: J27.42 (LED_WWAN#), LED9.C
unnamed: LED9.A, R102.2
SIM_CLK: J15.3 (CLK), J27.12 (UIM_CLK)
SIM_DATA: J15.7 (I/O), J27.10 (UIM_DATA)
SIM_PWR: J15.1 (VCC), J15.6 (VPP), J27.8 (UIM_PWR)
SIM_RESET: J15.2 (RST), J27.14 (UIM_RESET)

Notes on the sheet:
13. Modem
MicroSIM socket

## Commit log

2020-01-01 Initial commit, add WIP hardware
2020-01-01 Add GPLv3 for license
2020-01-01 Swap EEPROM with QSPI Flash, still has 48-bit EUI
2020-01-02 Add JTAG connector
2020-01-05 Flesh out FTDI and RS232
2020-01-06 Start adding power supply
2020-01-12 Add LTE modem and flesh out CAN interface
2020-01-12 First stab at power supply
2020-01-13 Switch 3V3 LDO to fix compatibility with EN pins
2020-01-13 Add high side drivers
2020-01-26 Swap to simple CAN transciever, no wake on CAN functionality required
2020-01-27 Add digital inputs, connect MCU power supply
2020-01-29 Start standing up some SW infra
2020-01-30 Bare bone example that compiles using GCC
2020-01-31 Add FreeRTOS
2020-02-01 Add CMSIS and HAL
2020-02-02 Fix connection between MCU and switch
2020-02-02 Add Debug LEDs
2020-02-03 Add schematic for test tool based on the full vehicle control module design
2020-02-22 Add missing oscillator, start to layout testtool board
2020-02-23 Finish placing components for testtool
2020-03-08 Finish laying out the test tool
2020-03-08 Fix silkscreen
2020-03-13 Add BOM for testtool
2020-05-19 First working bringup of board SW on FreeRTOS
2020-09-07 Add HAL, HPL and Lua
2020-09-25 Revert to ASF3
2020-09-27 Change to statically allocated tasks
2020-09-28 Additional cleanup
2020-09-30 Get unique ID working
2020-09-30 Allow specifying build type via CMake
2020-10-03 Read MAC address from EEPROM
2020-10-08 Bare bones bringup of GMAC with FreeRTOS
2020-10-09 Add reset cause
2020-10-10 Add hacky FreeRTOS-Plus-TCP port
2020-11-09 Rev to FreeRTOS-TCP 2.3.1
2020-11-12 Hack up the zero-copy port layer bundled with FreeRTOS-TCP stack, working but requires cleanup
2020-11-16 Move example GMAC driver out from FreeRTOS portable and start cleaning it up. Add iperf server for testing.
2020-11-18 WIP more cleanup
2021-06-23 Working with SystemView
2021-06-23 Upgrade FreeRTOS IP stack
2021-06-24 Add very crude ADC support from ASF example
2021-06-30 Add linker script as a build dep
2021-07-19 Start to rough in ADC and PWM support for highsides
